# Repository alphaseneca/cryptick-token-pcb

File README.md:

# Cryptick Token Hardware PCB

Hardware schematics, 4-layer PCB layout, and manufacturing files for **Cryptick Token** — the 100% open-source biometric hardware security key and cryptographic hardware enclave.

---

## Hardware Highlights

- **Main Processing Unit**: Espressif ESP32-S3-WROOM-1 (N16R8) Dual-Core Xtensa LX7 @ 240 MHz with hardware cryptography accelerators (AES-256, SHA-256, RSA-3072, ECC point multiplication, TRNG) and 16 MB encrypted SPI Flash.
- **Biometric Security Enclave**: R558S optical/capacitive fingerprint sensor (508 DPI, 120 on-sensor template slots, hardware wake-on-touch interrupt on GPIO 16).
- **Physical WYSIWYS Display**: 0.96" 128x64 Monochrome OLED (SSD1306) on hardware I2C (Address 0x3C, SDA GPIO 8, SCL GPIO 9) for origin verification ("What You See Is What You Sign").
- **Physical Navigation**: 5-Way Tactile Navigation Switch (UP GPIO 7, DOWN GPIO 4, LEFT GPIO 6, RIGHT GPIO 5, CENTER GPIO 15) for tactile PIN entry, menu navigation, and physical user presence (UP) confirmation.
- **Wireless & Wired Interfaces**:
  - Bluetooth Low Energy (BLE 5.0) via onboard 2.4 GHz PCB antenna.
  - Native USB Type-C Receptacle (USB 2.0 Full-Speed OTG) with bidirectional TVS diode ESD protection (USBLC6-2SC6).
- **Power Management**:
  - TP4056 / BQ24040 LiPo/Li-Ion linear battery charge management with dual status monitoring (STAT1 GPIO 38, STAT2 GPIO 39).
  - High-efficiency 3.3V LDO regulator with low quiescent current for ultra-deep sleep.
  - WS2812B Addressable RGB Neopixel LED on GPIO 48 for device status.

---

## PCB Specifications

| Parameter | Specification |
| :--- | :--- |
| **Dimensions** | 56.0 mm × 24.0 mm × 1.6 mm |
| **Layer Count** | 4 Layers (Signal / GND Plane / 3.3V Power Plane / Signal) |
| **Copper Weight** | 1 oz Outer, 1 oz Inner |
| **Min Trace / Space** | 0.127 mm / 0.127 mm (5/5 mil) |
| **Surface Finish** | ENIG (Electroless Nickel Immersion Gold) - RoHS compliant |
| **Solder Mask** | Matte Black with Gold Traces |
| **Silkscreen** | High-definition White |
| **Design Rules** | JLCPCB 4-Layer Standard Impedance (JLC04161H-7628) |

---

## Schematic & Manufacturing Files

- Schematic source: `cryptick-token-pcb.kicad_sch`
- Board layout: `cryptick-token-pcb.kicad_pcb`
- KiCad project: `cryptick-token-pcb.kicad_pro`
- Automated releases produce:
  - Gerber RS-274X drill and layer files (`gerbers.zip`)
  - Bill of Materials (BOM) in JLCPCB SMT format (`bom.csv`)
  - Pick and Place Component Centroid coordinates (`pos.csv`)

---

## Automated Tag Release

Pushing any semantic version tag (e.g. `v0.1.0`) triggers `.github/workflows/release.yml`, executing [KiForge](https://github.com/alphaseneca/kiforge) in CI to automatically generate and attach production fabrication assets to GitHub Releases.

---

## Part of the Cryptick Token Ecosystem

- [Main Consolidated Repository](https://github.com/alphaseneca/cryptick-token)
- [Firmware & Core Logic](https://github.com/alphaseneca/cryptick-token-code)
- [Host Daemon, CLI & SmartCard PIV](https://github.com/alphaseneca/cryptick-token-daemon)
- [Browser Extension](https://github.com/alphaseneca/cryptick-token-extension)

---

## License

Hardware schematics and PCB designs are licensed under the [MIT License](LICENSE) / CERN Open Hardware Licence.

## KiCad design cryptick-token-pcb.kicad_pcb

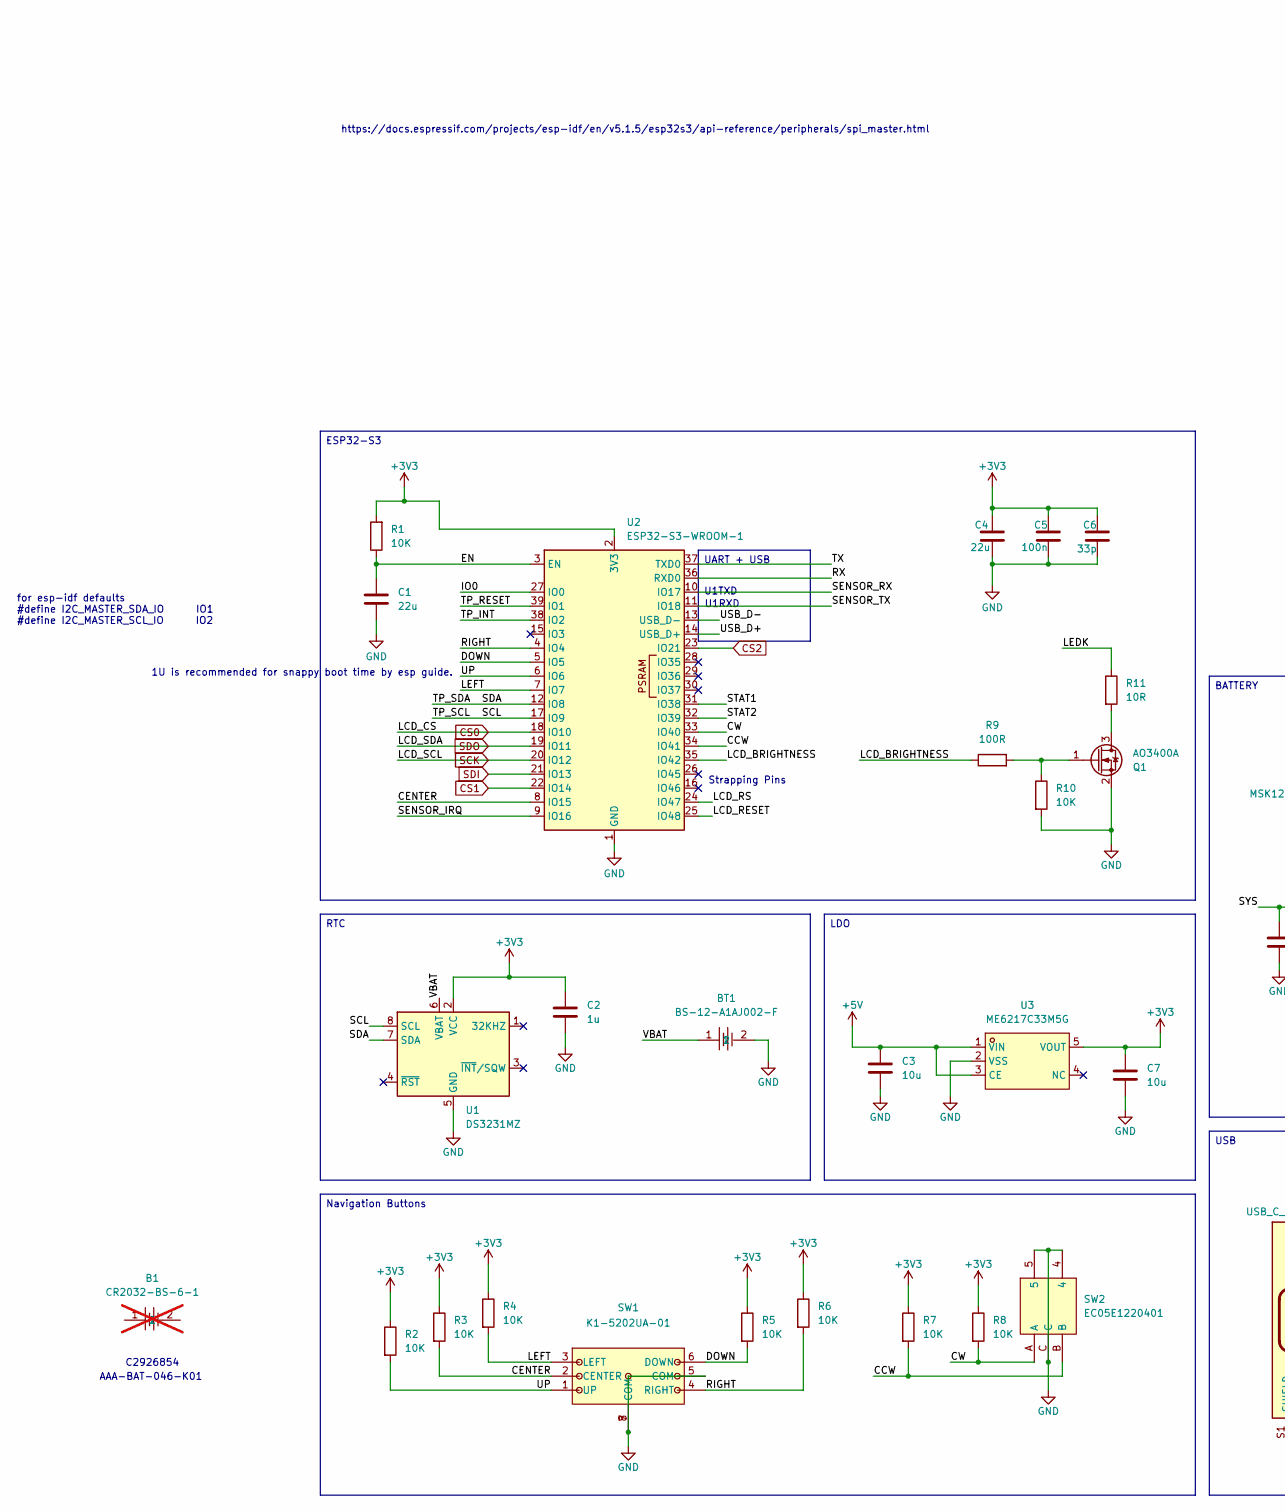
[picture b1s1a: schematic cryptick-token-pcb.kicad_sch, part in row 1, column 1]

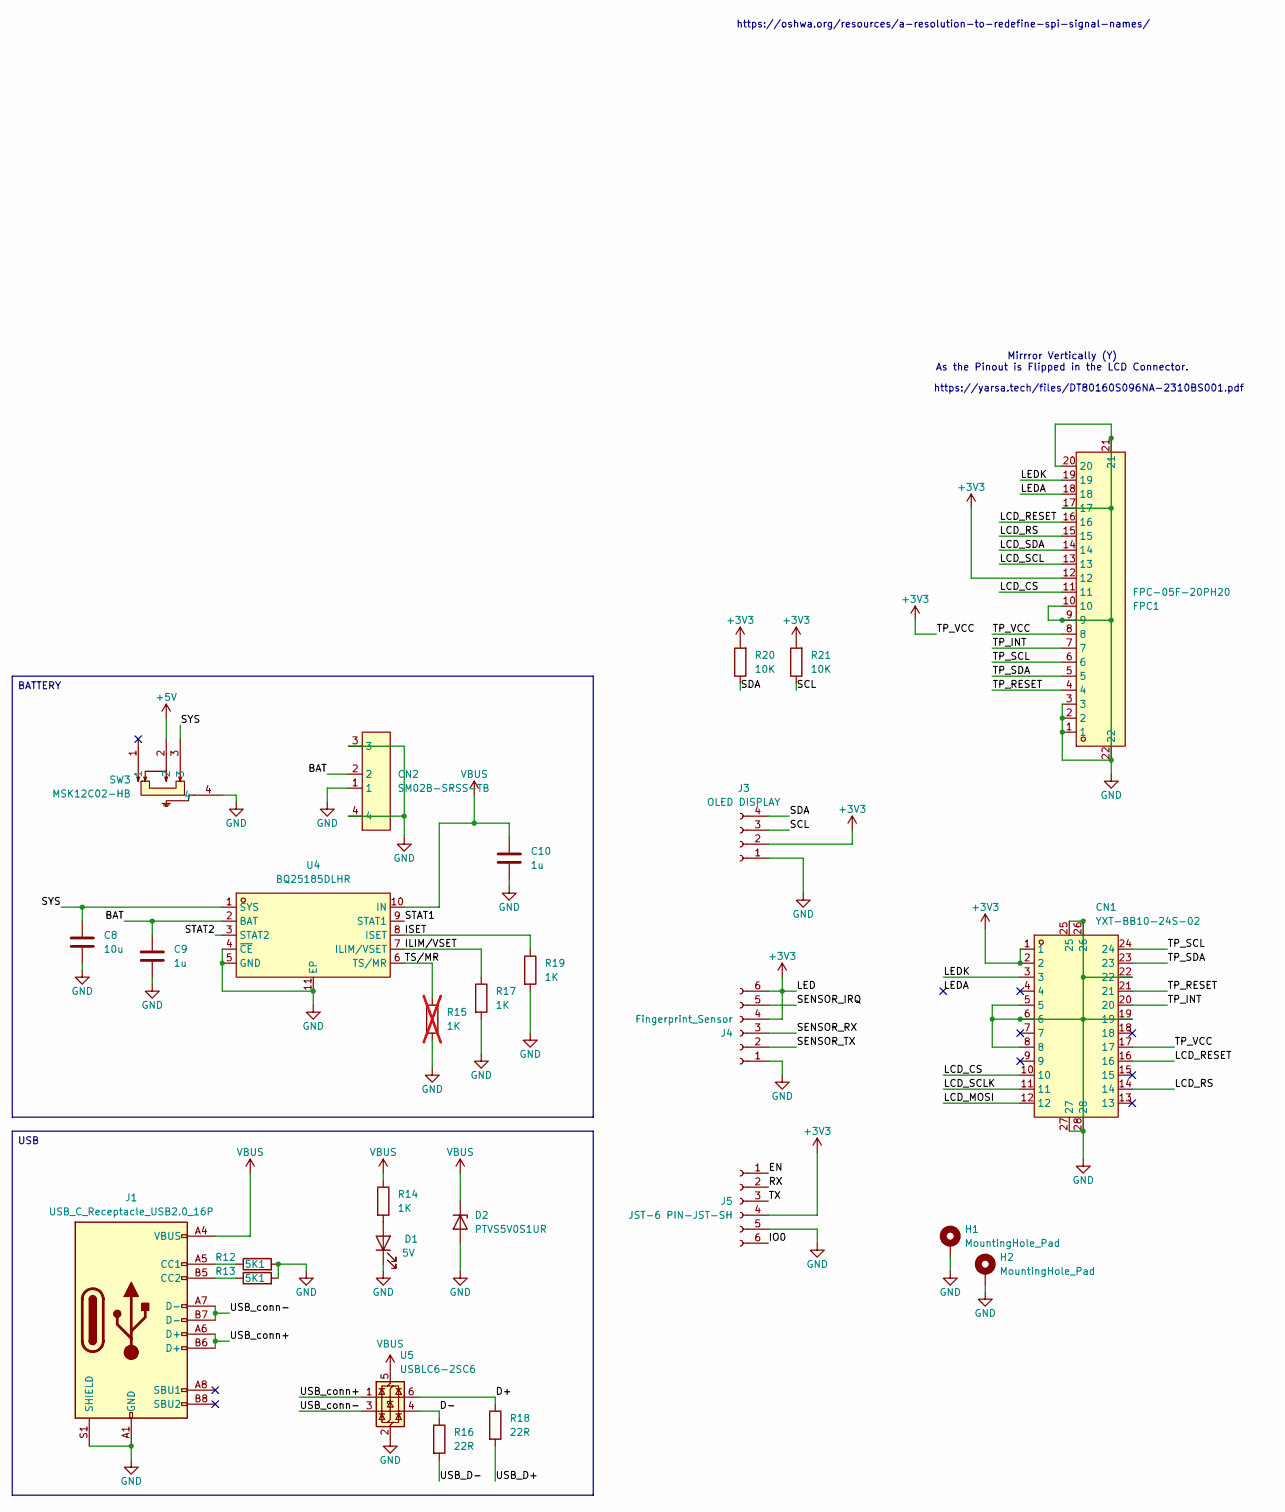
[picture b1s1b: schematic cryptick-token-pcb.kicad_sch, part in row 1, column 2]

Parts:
B1: CR2032-BS-6-1; BAT-TH_CR2032-BS-6-1; MPN CR2032-BS-6-1; not fitted
BT1: BS-12-A1AJ002-F; BAT-TH_BS-12-A1AJ002-F; MPN BS-12-A1AJ002-F
C1, C4: 22u; C_0805_2012Metric; MPN CL21A226MAYNNNE
C2, C9, C10: 1u; C_0805_2012Metric; MPN CL21B105KBFNNNE
C3, C7, C8: 10u; C_0805_2012Metric; MPN CL21A106KAYNNNE
C5: 100n; C_0603_1608Metric; MPN CL10B104KB8NNNC
C6: 33p; C_0603_1608Metric; MPN CL10C330JB8NNNC
CN1: YXT-BB10-24S-02; CONN-SMD_YXT-BB10-24S-02; MPN YXT-BB10-24S-02
CN2: SM02B-SRSS-TB; CONN-SMD_2P-P1.00_SM02B-SRSS-TB-LF-SN; MPN 1.0-2PWB
D1: 5V; LED_0603_1608Metric; MPN XL-1608SURC-06
D2: PTVS5V0S1UR; D_SOD-123; MPN PTVS5V0S1UR,115
FPC1: FPC-05F-20PH20; FPC-SMD_20P-P0.50_XUNPU_FPC-05F-20PH20; MPN FC05-S20DCT-00
H1, H2: MountingHole_Pad; MountingHole_2.2mm_M2_Pad_Via
J1: USB_C_Receptacle_USB2.0_16P; USB_C_Receptacle_G-Switch_GT-USB-7010ASV; MPN TYPE-C 16PIN 2MD(073)
J3: OLED DISPLAY; PinHeader_1x04_P2.54mm_Vertical
J4: Fingerprint_Sensor; JST_SH_BM06B-SRSS-TB_1x06-1MP_P1.00mm_Vertical; MPN 1.0-6PS
J5: JST-6 PIN-JST-SH; JST_SH_BM06B-SRSS-TB_1x06-1MP_P1.00mm_Vertical; MPN 1.0-6PS
Q1: AO3400A; SOT-23; MPN AO3400A
R1, R2, R3, R4, R5, R6, R7, R8, R10, R20, R21: 10K; R_0603_1608Metric; MPN RC0603FR-0710KL
R9: 100R; R_0603_1608Metric; MPN RC0603FR-07100RL
R11: 10R; R_0603_1608Metric; MPN RC0603FR-0710RL
R12, R13: 5K1; R_0603_1608Metric; MPN RC0603FR-075K1L
R14, R17, R19: 1K; R_0603_1608Metric; MPN RC0603FR-071KL
R15: 1K; R_0603_1608Metric; MPN RC0603FR-071KL; not fitted
R16, R18: 22R; R_0603_1608Metric; MPN RC0603FR-0722RL
SW1: K1-5202UA-01; SW-SMD_K1-5202UA-01; MPN K1-5202UA-01
SW2: EC05E1220401; SW-SMD_EC05E1220401; MPN EC05E1220401
SW3: MSK12C02-HB; SW-TH_MSK12C02-HB-1; MPN MSK12C02-HB
U1: DS3231MZ; SOIC-8_3.9x4.9mm_P1.27mm; MPN DS3231MZ+TRL
U2: ESP32-S3-WROOM-1
U3: ME6217C33M5G; SOT-23-5_L3.0-W1.7-P0.95-LS2.8-BR; MPN ME6217C33M5G
U4: BQ25185DLHR; WSON-10_L2.2-W2.0-P0.40-BL-EP_TI_DLH0010A; MPN BQ25185DLHR
U5: USBLC6-2SC6; SOT-23-6; MPN USBLC6-2SC6

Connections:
+3V3: C2.1, C4.1, C5.1, C6.1, C7.1, CN1.1, CN1.2, CN1.17, FPC1.8, FPC1.12, J3.2, J4.4, J4.6, J5.4, R1.2, R2.1, R3.1, R4.1, R5.1, R6.1, R7.1, R8.1, R20.2, R21.2, U1.2 (VCC), U2.2 (3V3), U3.5 (VOUT)
+5V: C3.1, SW3.2, U3.1 (VIN), U3.3 (CE)
/BAT: C9.1, CN2.2, U4.2 (BAT)
/CCW: R7.2, SW2.B, U2.34 (IO41)
/CENTER: R3.2, SW1.2 (CENTER), U2.8 (IO15)
/CW: R8.2, SW2.A, U2.33 (IO40)
/D+: R18.1, U5.6 (I/O1)
/D-: R16.1, U5.4 (I/O2)
/DOWN: R5.2, SW1.6 (DOWN), U2.5 (IO5)
/EN: C1.1, J5.1, R1.1, U2.3 (EN)
/ILIM/VSET: R17.1, U4.7 (ILIM/VSET)
/IO0: J5.6, U2.27 (IO0)
/ISET: R19.1, U4.8 (ISET)
/LCD_BRIGHTNESS: R9.1, U2.35 (IO42)
/LCD_MOSI: CN1.12
/LCD_RESET: CN1.16, FPC1.16, U2.25 (IO48)
/LCD_RS: CN1.14, FPC1.15, U2.24 (IO47)
/LCD_SCLK: CN1.11
/LEDA: FPC1.18
/LEDK: CN1.3, FPC1.19, R11.1
/LEFT: R4.2, SW1.3 (LEFT), U2.7 (IO7)
/RIGHT: R6.2, SW1.4 (RIGHT), U2.4 (IO4)
/RX: J5.2, U2.36 (RXD0)
/SCL: CN1.24, FPC1.6, J3.3, R21.1, U1.8 (SCL), U2.17 (IO9)
/SDA: CN1.23, FPC1.5, J3.4, R20.1, U1.7 (SDA), U2.12 (IO8)
/SENSOR_IRQ: J4.5, U2.9 (IO16)
/SENSOR_RX: J4.3, U2.10 (IO17)
/SENSOR_TX: J4.2, U2.11 (IO18)
/STAT1: U2.31 (IO38), U4.9 (STAT1)
/STAT2: U2.32 (IO39), U4.3 (STAT2)
/SYS: C8.1, SW3.3, U4.1 (SYS)
/TP_INT: CN1.20, FPC1.7, U2.38 (IO2)
/TP_RESET: CN1.21, FPC1.4, U2.39 (IO1)
/TS/MR: R15.1, U4.6 (TS/MR)
/TX: J5.3, U2.37 (TXD0)
/UP: R2.2, SW1.1 (UP), U2.6 (IO6)
/USB_D+: R18.2, U2.14 (USB_D+)
/USB_D-: R16.2, U2.13 (USB_D-)
/USB_conn+: J1.A6 (D+), J1.B6 (D+), U5.1 (I/O1)
/USB_conn-: J1.A7 (D-), J1.B7 (D-), U5.3 (I/O2)
/VBAT: BT1.1, U1.6 (VBAT)
CS0: CN1.10, FPC1.11, U2.18 (IO10)
CS1: U2.22 (IO14)
CS2: U2.23 (IO21)
GND: BT1.2, C1.2, C2.2, C3.2, C4.2, C5.2, C6.2, C7.2, C8.2, C9.2, C10.2, CN1.5, CN1.6, CN1.8, CN1.19, CN1.22, CN1.25, CN1.26, CN1.27, CN1.28, CN2.1, CN2.3, CN2.4, D1.1 (K), D2.2 (A), FPC1.1, FPC1.2, FPC1.3, FPC1.9, FPC1.10, FPC1.17, FPC1.20, FPC1.21, FPC1.22, H1.1 (1_1), H2.1 (1_1), J1.A1 (GND), J1.A12 (GND), J1.B1 (GND), J1.B12 (GND), J1.S1 (SHIELD), J3.1, J4.1, J5.5, Q1.2 (S), R10.2, R12.2, R13.2, R15.2, R17.2, R19.2, SW1.5 (COM), SW1.7 (COM), SW1.8 (COM), SW2.4, SW2.5, SW2.C, SW3.4, U1.5 (GND), U2.1 (GND), U2.40 (GND), U2.41 (GND), U3.2 (VSS), U4.4 (~CE), U4.5 (GND), U4.11 (EP), U5.2 (GND)
unnamed: D1.2 (A), R14.2
unnamed: J1.A5 (CC1), R12.1
unnamed: J1.B5 (CC2), R13.1
unnamed: Q1.3 (D), R11.2
unnamed: Q1.1 (G), R9.2, R10.1
SCK: FPC1.13, U2.20 (IO12)
SDI: U2.21 (IO13)
SDO: FPC1.14, U2.19 (IO11)
VBUS: C10.1, D2.1 (K), J1.A4 (VBUS), J1.A9 (VBUS), J1.B4 (VBUS), J1.B9 (VBUS), R14.1, U4.10 (IN), U5.5 (VBUS)

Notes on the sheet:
Strapping Pins
https://docs.espressif.com/projects/esp-idf/en/v5.1.5/esp32s3/api-reference/peripherals/spi_master.html
https://oshwa.org/resources/a-resolution-to-redefine-spi-signal-names/
https://yarsa.tech/files/DT80160S096NA-2310BS001.pdf
Mirrror Vertically (Y) As the Pinout is Flipped in the LCD Connector.
for esp-idf defaults #define I2C_MASTER_SDA_IO IO1 #define I2C_MASTER_SCL_IO IO2
C2926854
AAA-BAT-046-K01
1U is recommended for snappy boot time by esp guide.
U1RXD
U1TXD
UART + USB
LDO
USB
ESP32-S3
RTC
BATTERY
Navigation Buttons

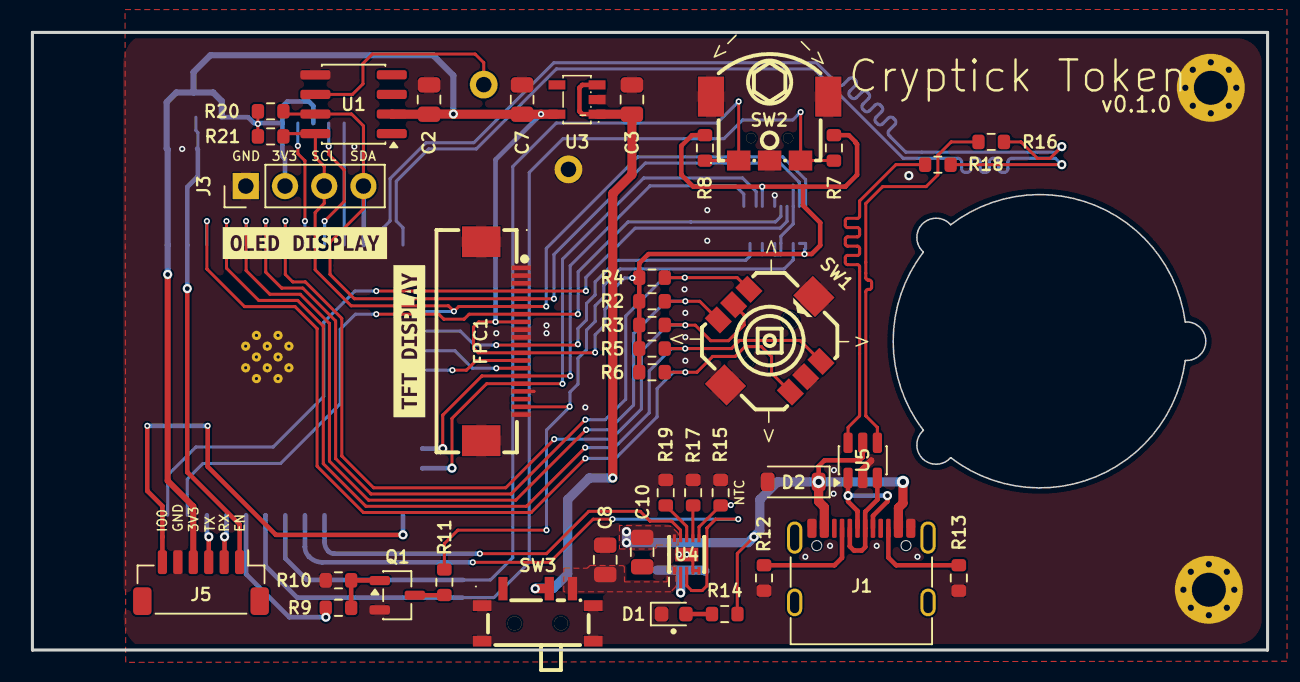
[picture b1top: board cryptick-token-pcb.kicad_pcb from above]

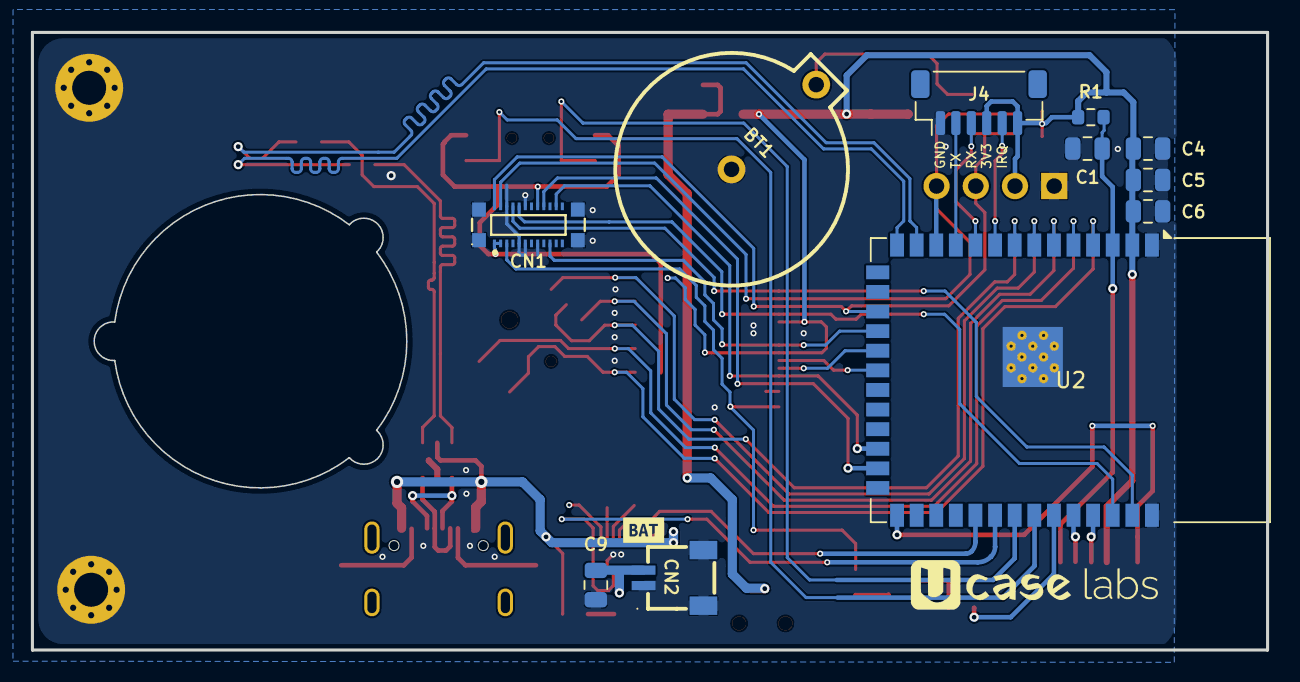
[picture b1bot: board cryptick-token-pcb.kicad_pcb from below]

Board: 2 copper layers, 80.0 x 40.0 mm, 55 parts (12 on the bottom side), 48 nets.

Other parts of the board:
kibuzzard-6A344DA8: G***; kibuzzard-6A344DA8
kibuzzard-6A3445EB: G***; kibuzzard-6A3445EB
kibuzzard-6A344627: G***; kibuzzard-6A344627

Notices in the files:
README.md:
License: MIT
